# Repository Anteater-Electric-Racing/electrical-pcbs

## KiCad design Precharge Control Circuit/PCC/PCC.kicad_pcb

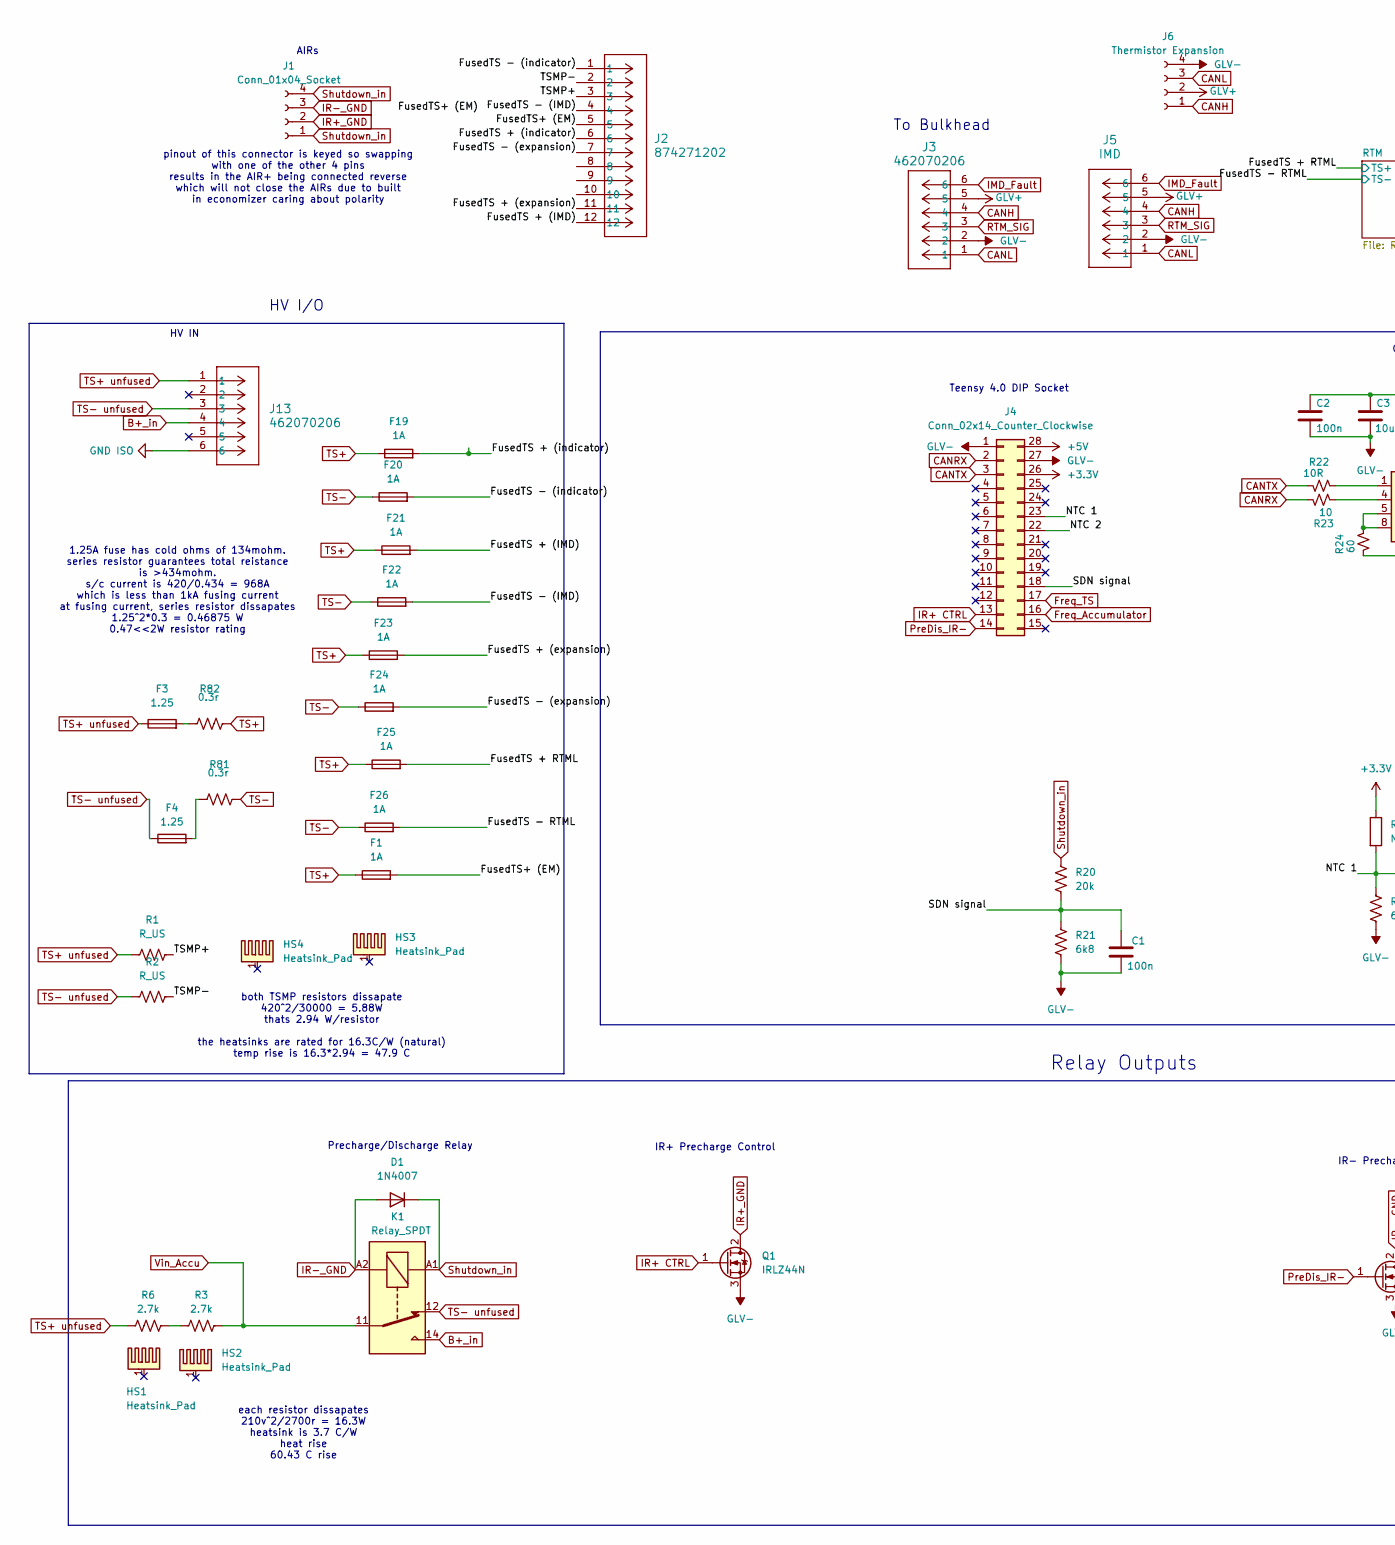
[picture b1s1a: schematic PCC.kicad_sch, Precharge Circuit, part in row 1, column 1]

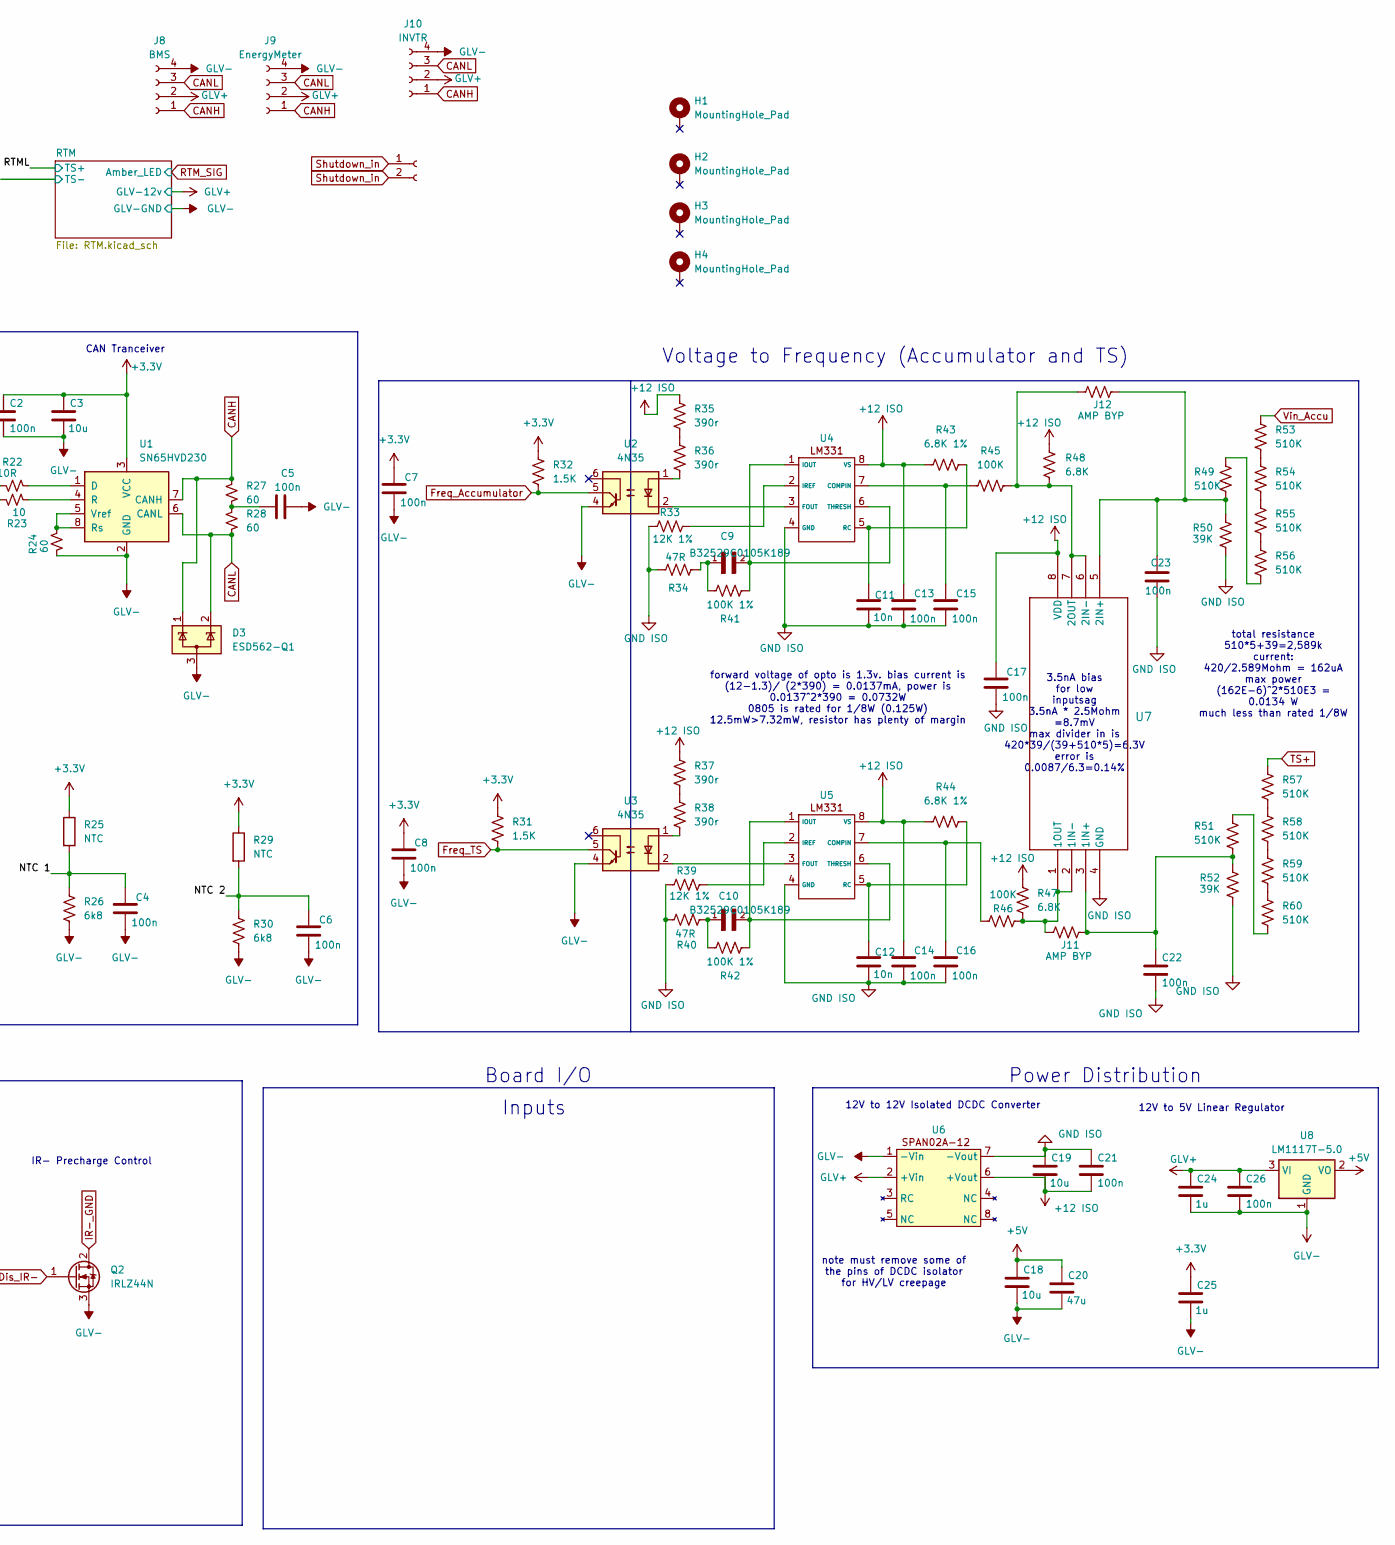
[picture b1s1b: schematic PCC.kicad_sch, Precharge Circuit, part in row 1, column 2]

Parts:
C1, C2, C4, C6, C7, C8, C13, C14, C15, C16, C17, C21, C22, C26: 100n; C_0805_2012Metric; MPN CC0805KRX7R9BB104
C3, C18, C19: 10u; C_0805_2012Metric; MPN EMK212BJ106KG-T
C5, C23: 100n; C_0805_2012Metric
C9, C10: B32529C0105K189; CAPRR500W50L730T450H950; PARTREV 2020-06; DigiKey_Part_Number 495-B32529C0105K189CT-ND
C11, C12: 10n; C_0805_2012Metric; MPN CL21B103KBANNNC
C20: 47u; C_0805_2012Metric; MPN GRM21BR61A476ME15K
C24, C25: 1u; C_0805_2012Metric; MPN CL21B105KBFNNNE
D1: 1N4007; D_DO-41_SOD81_P10.16mm_Horizontal; MPN 1N4007
D3: ESD562-Q1; SOT-23-3; MPN ESD562DBZRQ1
F1, F19, F20, F21, F22, F23, F24, F25, F26: 1A; 5x20fuseblock; MPN 0031.8222
F3, F4: 1.25; 5x20fuseblock; MPN 0031.8222
H1, H2, H3, H4: MountingHole_Pad; MountingHole_3.2mm_M3_DIN965_Pad_TopBottom
HS1, HS2: Heatsink_Pad; heatsink; MPN 529802B02500G
HS3, HS4: Heatsink_Pad; smolsink; MPN HSS-B20-0503H
J1: Conn_01x04_Socket; Molex_Mini-Fit_Jr_5566-04A2_2x02_P4.20mm_Vertical
J2: 874271202; 12pSTminifit
J3, J13: 462070206; 6pMinifitJR
J4: Conn_02x14_Counter_Clockwise; DIP-28_W15.24mm_Socket; MPN 110-44-628-41-001000
J5: IMD; 6pMinifitJR
J6: Thermistor Expansion; Molex_Mini-Fit_Jr_5566-04A2_2x02_P4.20mm_Vertical
J8: BMS; Molex_Mini-Fit_Jr_5566-04A2_2x02_P4.20mm_Vertical
J9: EnergyMeter; Molex_Mini-Fit_Jr_5566-04A2_2x02_P4.20mm_Vertical
J10: INVTR; Molex_Mini-Fit_Jr_5566-04A2_2x02_P4.20mm_Vertical
J11, J12: AMP BYP; R_0805_2012Metric
K1: Relay_SPDT; Precharge_Discharge_Relay_Rincon
Q1, Q2: IRLZ44N; TO-220-3_Horizontal_TabDown; MPN IRLZ44NPBF
R1, R2: R_US; TO-220-2_Vertical-SMD; MPN PWR220T-35-1502J
R3, R6: 2.7k; TO-220-2_Vertical; MPN RTO020F27000JTE3
R20: 20k; R_0805_2012Metric
R21, R26, R30: 6k8; R_0805_2012Metric
R22: 10R; R_0805_2012Metric
R23: 10; R_0805_2012Metric
R24, R27, R28: 60; R_0805_2012Metric
R25, R29: NTC; PinSocket_1x02_P2.00mm_Vertical
R31, R32: 1.5K; R_0805_2012Metric; MPN ERJ-6GEYJ152V
R33, R39: 12K 1%; R_0805_2012Metric; MPN CRG0805F12K
R34, R40: 47R; R_0805_2012Metric; MPN RC0805JR-0747RL
R35, R36, R37, R38: 390r; R_0805_2012Metric; MPN RC0805FR-7W390RL
R41, R42: 100K 1%; R_0805_2012Metric; MPN RMCF0805FG100K
R43, R44: 6.8K 1%; R_0805_2012Metric; MPN RC0805FR-076K8L
R45, R46: 100K; R_0805_2012Metric; MPN RMCF0805FG100K
R47, R48: 6.8K; R_0805_2012Metric; MPN RC0805FR-076K8L
R49, R51, R53, R54, R55, R56, R57, R58, R59, R60: 510K; R_0805_2012Metric; MPN ERJ-6GEYJ514V
R50, R52: 39K; R_0805_2012Metric; MPN ERJ-6GEYJ393V
R81, R82: 0.3r; R_2512_6332Metric_Pad1.40x3.35mm_HandSolder; MPN CSRN2512FKR300
SDC1: Conn_01x02_Socket; Molex_Mini-Fit_Jr_5566-02A2_2x01_P4.20mm_Vertical
U1: SN65HVD230; SOIC-8_3.9x4.9mm_P1.27mm; MPN SN65HVD230DR
U2, U3: 4N35; DIP-6_W7.62mm_Socket
U4, U5: DIP-8_W7.62mm_Socket; MPN Texas Instruments
U6: isoDCDC(removedPins); MPN SPAN02A-12
U7: TLV2372IP; P8; MPN TLV2372IP
U8: LM1117T-5.0; TO-220-3_Horizontal_TabDown; MPN LM1117T-5.0/NOPB

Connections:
+3.3V: C2.1, C3.1, C7.1, C8.1, C25.1, J4.26, R25.1, R29.1, R31.2, R32.2, U1.3 (VCC)
+5V: C18.1, C20.1, J4.28, U8.2 (VO)
+12 ISO: C13.1, C14.1, C17.1, C19.2, C21.2, R35.2, R37.2, R43.1, R44.1, R47.2, R48.2, U4.8 (VS), U5.8 (VS), U6.6 (+Vout), U7.8 (VDD)
/FusedTS + (IMD): F21.2, J2.12
/FusedTS + (expansion): F23.2, J2.11
/FusedTS + (indicator): F19.2, J2.6
/FusedTS - (IMD): F22.2, J2.4
/FusedTS - (expansion): F24.2, J2.7
/FusedTS - (indicator): F20.2, J2.1
/FusedTS+ (EM): F1.2, J2.5
/NTC 1: C4.1, J4.23, R25.2, R26.1
/NTC 2: C6.1, J4.22, R29.2, R30.1
/SDN signal: C1.1, J4.18, R20.2, R21.1
/TSMP+: J2.3, R1.1
/TSMP-: J2.2, R2.1
B+_in: J13.4, K1.14
CANH: D3.1 (K), J3.4, J5.4, J6.1, J8.1, J9.1, J10.1, R27.1, U1.7 (CANH)
CANL: D3.2 (K), J3.1, J5.1, J6.3, J8.3, J9.3, J10.3, R28.2, U1.6 (CANL)
CANRX: J4.2, R23.1
CANTX: J4.3, R22.2
Freq_Accumulator: J4.16, R32.1, U2.5
Freq_TS: J4.17, R31.1, U3.5
GLV+: C24.1, C26.1, J3.5, J5.5, J6.2, J8.2, J9.2, J10.2, U6.2 (+Vin), U8.3 (VI); also elsewhere on the board
GLV-: C1.2, C2.2, C3.2, C4.2, C5.2, C6.2, C7.2, C8.2, C18.2, C20.2, C24.2, C25.2, C26.2, D3.3 (A), J3.2, J4.1, J4.27, J5.2, J6.4, J8.4, J9.4, J10.4, Q1.3 (S), Q2.3 (S), R21.2, R24.2, R26.2, R30.2, U1.2 (GND), U2.4, U3.4, U6.1 (-Vin), U8.1 (GND); also elsewhere on the board
GND ISO: C11.2, C12.2, C13.2, C14.2, C15.2, C16.2, C17.2, C19.1, C21.1, C22.2, C23.2, J13.6, R33.1, R34.2, R39.1, R40.2, R50.2, R52.2, U4.4 (GND), U5.4 (GND), U6.7 (-Vout), U7.4 (GND)
HighVoltage+: F25.2; also elsewhere on the board
HighVoltage-: F26.2; also elsewhere on the board
IMD_Fault: J3.6, J5.6
IR+ CTRL: J4.13, Q1.1 (G)
IR+_GND: J1.2, Q1.2 (D)
IR-_GND: D1.2 (A), J1.3, K1.A2, Q2.2 (D)
unnamed: C5.1, R27.2, R28.1
unnamed: C9.1, R34.1, R41.1
unnamed: C10.1, R40.1, R42.1
unnamed: F3.2, R82.1
unnamed: F4.2, R81.1
unnamed: R3.1, R6.2
unnamed: R35.1, R36.2
unnamed: R36.1, U2.1
unnamed: R37.1, R38.2
unnamed: R38.1, U3.1
unnamed: R49.1, R56.2
unnamed: R51.1, R60.2
unnamed: R53.2, R54.1
unnamed: R54.2, R55.1
unnamed: R55.2, R56.1
unnamed: R57.2, R58.1
unnamed: R58.2, R59.1
unnamed: R59.2, R60.1
unnamed: R22.1, U1.1 (D)
unnamed: R23.2, U1.4 (R)
unnamed: R24.1, U1.5 (Vref), U1.8 (Rs)
unnamed: C15.1, R45.1, U4.7 (COMPIN)
unnamed: U2.2, U4.3 (FOUT)
unnamed: C9.2, R41.2, U4.1 (IOUT), U4.6 (THRESH)
unnamed: R33.2, U4.2 (IREF)
unnamed: C11.1, R43.2, U4.5 (RC)
unnamed: C16.1, R46.1, U5.7 (COMPIN)
unnamed: U3.2, U5.3 (FOUT)
unnamed: C10.2, R42.2, U5.1 (IOUT), U5.6 (THRESH)
unnamed: R39.2, U5.2 (IREF)
unnamed: C12.1, R44.2, U5.5 (RC)
unnamed: C22.1, J11.2, R51.2, R52.1, U7.3 (1IN+)
unnamed: J11.1, R46.2, R47.1, U7.1 (1OUT), U7.2 (1IN-)
unnamed: C23.1, J12.2, R49.2, R50.1, U7.5 (2IN+)
unnamed: J12.1, R45.2, R48.1, U7.6 (2IN-), U7.7 (2OUT)
PreDis_IR-: J4.14, Q2.1 (G)
RTM_SIG: J3.3, J5.3; also elsewhere on the board
Shutdown_in: D1.1 (K), J1.1, J1.4, K1.A1, R20.1, SDC1.1, SDC1.2
TS+: F1.1, F19.1, F21.1, F23.1, F25.1, R57.1, R82.2
TS+ unfused: F3.1, J13.1, R1.2, R6.1
TS-: F20.1, F22.1, F24.1, F26.1, R81.2
TS- unfused: F4.1, J13.3, K1.12, R2.2
Vin_Accu: K1.11, R3.2, R53.1

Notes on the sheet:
Board I/O
HV IN
HV I/O
total resistance 510*5+39=2,589k current: 420/2.589Mohm = 162uA max power (162E-6)^2*510E3 = 0.0134 W much less than rated 1/8W
Inputs
1.25A fuse has cold ohms of 134mohm. series resistor guarantees total reistance is >434mohm. s/c current is 420/0.434 = 968A which is less than 1kA fusing current at fusing current, series resistor dissapates 1.25^2*0.3 = 0.46875 W 0.47<<2W resistor rating
forward voltage of opto is 1.3v. bias current is (12-1.3)/ (2*390) = 0.0137mA, power is 0.0137^2*390 = 0.0732W 0805 is rated for 1/8W (0.125W) 12.5mW>7.32mW, resistor has plenty of margin
AIRs
each resistor dissapates 210v^2/2700r = 16.3W heatsink is 3.7 C/W heat rise 60.43 C rise
both TSMP resistors dissapate 420^2/30000 = 5.88W thats 2.94 W/resistor the heatsinks are rated for 16.3C/W (natural) temp rise is 16.3*2.94 = 47.9 C
To Bulkhead
Teensy 4.0 DIP Socket
IR- Precharge Control
Voltage to Frequency (Accumulator and TS)
3.5nA bias for low inputsag 3.5nA * 2.5Mohm =8.7mV max divider in is 420*39/(39+510*5)=6.3V error is 0.0087/6.3=0.14%
Relay Outputs
CAN Tranceiver
Precharge/Discharge Relay
note must remove some of the pins of DCDC isolator for HV/LV creepage
IR+ Precharge Control
Power Distribution
pinout of this connector is keyed so swapping with one of the other 4 pins results in the AIR+ being connected reverse which will not close the AIRs due to built in economizer caring about polarity
12V to 5V Linear Regulator
12V to 12V Isolated DCDC Converter

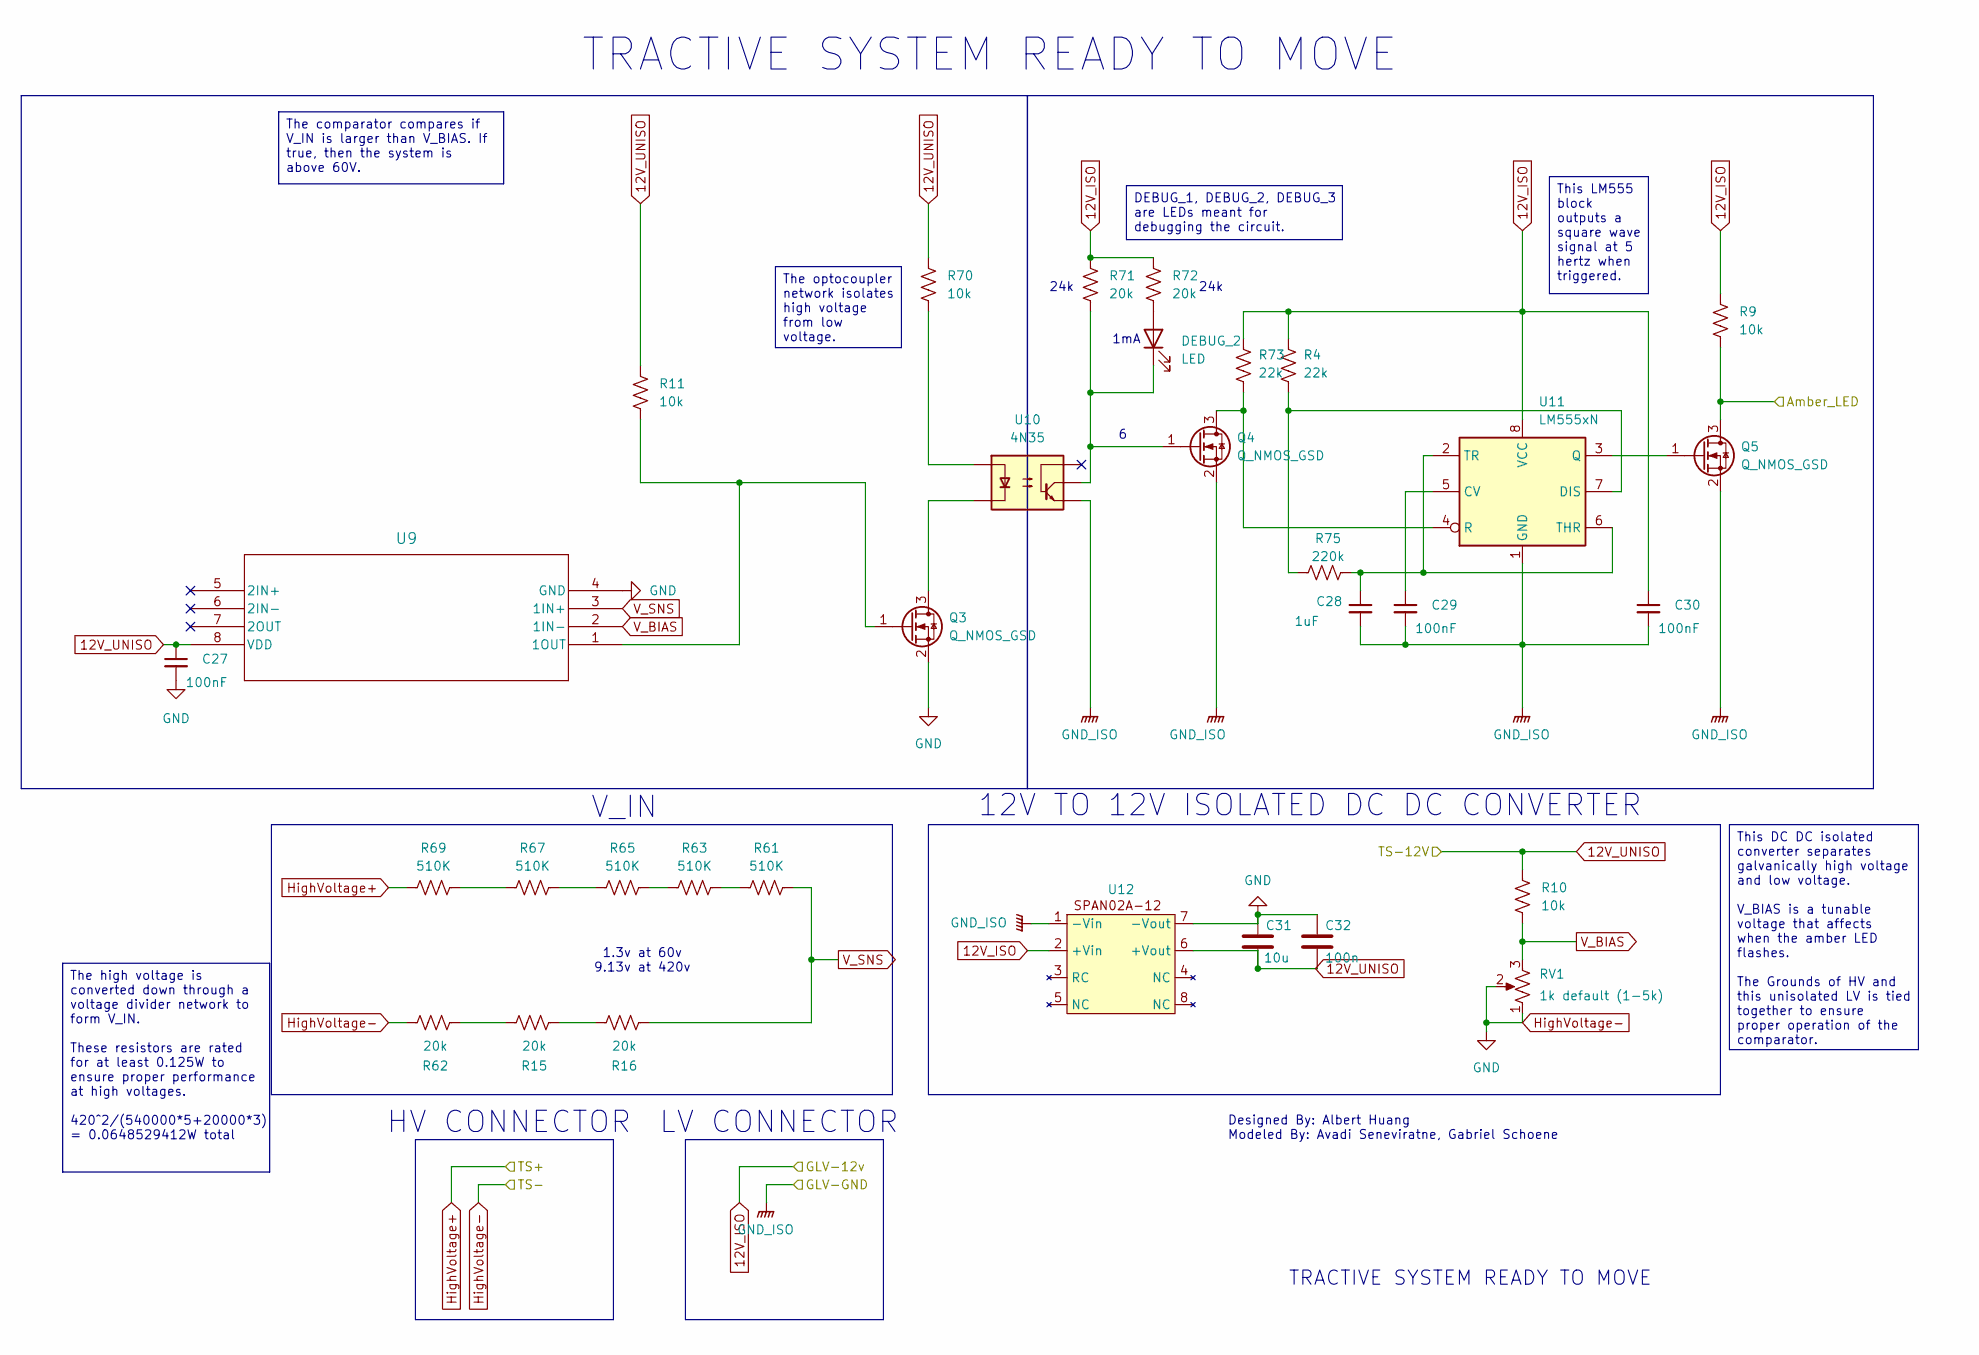
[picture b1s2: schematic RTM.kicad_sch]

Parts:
C27, C29, C30: 100nF; C_0805_2012Metric; MPN 08055C104J4T4A
C28: 1uF; C_0805_2012Metric; MPN CC0805JKX7R9BB105
C31: 10u; C_0805_2012Metric; MPN EMK212BJ106KG-T
C32: 100n; C_0805_2012Metric; MPN CC0805KRX7R9BB104
DEBUG_2: LED; LED_D5.0mm; MPN SLR-56VC3F
Q3, Q4, Q5: Q_NMOS_GSD; SOT-23; MPN SI2304A
R4, R73: 22k; R_0805_2012Metric; MPN RPC0805JT22R0
R9, R10, R11, R70: 10k; R_0805_2012Metric; MPN RC0805FR-7W10KL
R15, R16, R62: 20k; R_0805_2012Metric; MPN RC0805FR-0720KL
R61, R63, R65, R67, R69: 510K; R_0805_2012Metric; MPN ERJ-6GEYJ514V
R71, R72: 20k; R_0805_2012Metric
R75: 220k; R_0805_2012Metric; MPN RC0805FR-7W220KL
RV1: 1k default (1-5k); Potentiometer_Bourns_3296Y_Vertical; MPN 3296Y-1-502LF
U9: TLV2372IP; P8; MPN TLV2372IP
U10: 4N35; DIP-6_W7.62mm; MPN Lite-On Inc.
U11: LM555xN; DIP-8_W7.62mm
U12: isoDCDC(removedPins); MPN SPAN02A-12

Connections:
12V_UNISO: C27.1, C31.2, C32.2, R10.1, R11.1, R70.1, U9.8 (VDD), U12.6 (+Vout)
GLV+: C30.1, R4.1, R9.1, R71.1, R72.1, R73.1, U11.8 (VCC), U12.2 (+Vin); also elsewhere on the board
GLV-: C28.2, C29.2, C30.2, Q4.2 (S), Q5.2 (S), U10.4, U11.1 (GND), U12.1 (-Vin); also elsewhere on the board
HighVoltage+: R69.1; also elsewhere on the board
HighVoltage-: C27.2, C31.1, C32.1, Q3.2 (S), R62.2, RV1.1, RV1.2, U9.4 (GND), U12.7 (-Vout); also elsewhere on the board
unnamed: DEBUG_2.2 (A), R72.2
unnamed: DEBUG_2.1 (K), Q4.1 (G), R71.2, U10.5
unnamed: Q3.3 (D), U10.2
unnamed: Q3.1 (G), R11.2, U9.1 (1OUT)
unnamed: Q4.3 (D), R73.2, U11.4 (R)
unnamed: Q5.1 (G), U11.3 (Q)
unnamed: R15.1, R16.2
unnamed: R15.2, R62.1
unnamed: R61.1, R63.2
unnamed: R63.1, R65.2
unnamed: R65.1, R67.2
unnamed: R67.1, R69.2
unnamed: R70.2, U10.1
unnamed: C29.1, U11.5 (CV)
unnamed: R4.2, R75.1, U11.7 (DIS)
unnamed: C28.1, R75.2, U11.2 (TR), U11.6 (THR)
RTM_SIG: Q5.3 (D), R9.2; also elsewhere on the board
V_BIAS: R10.2, RV1.3, U9.2 (1IN-)
V_SNS: R16.1, R61.2, U9.3 (1IN+)

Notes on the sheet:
12V TO 12V ISOLATED DC DC CONVERTER
V_IN
1.3v at 60v 9.13v at 420v
TRACTIVE SYSTEM READY TO MOVE
24k
1mA
24k
LV CONNECTOR
TRACTIVE SYSTEM READY TO MOVE
Designed By: Albert Huang Modeled By: Avadi Seneviratne, Gabriel Schoene
HV CONNECTOR
This DC DC isolated converter separates galvanically high voltage and low voltage. V_BIAS is a tunable voltage that affects when the amber LED flashes. The Grounds of HV and this unisolated LV is tied together to ensure proper operation of the comparator.
The comparator compares if V_IN is larger than V_BIAS. If true, then the system is above 60V.
The high voltage is converted down through a voltage divider network to form V_IN. These resistors are rated for at least 0.125W to ensure proper performance at high voltages. 420^2/(540000*5+20000*3) = 0.0648529412W total
This LM555 block outputs a square wave signal at 5 hertz when triggered.
DEBUG_1, DEBUG_2, DEBUG_3 are LEDs meant for debugging the circuit.
The optocoupler network isolates high voltage from low voltage.

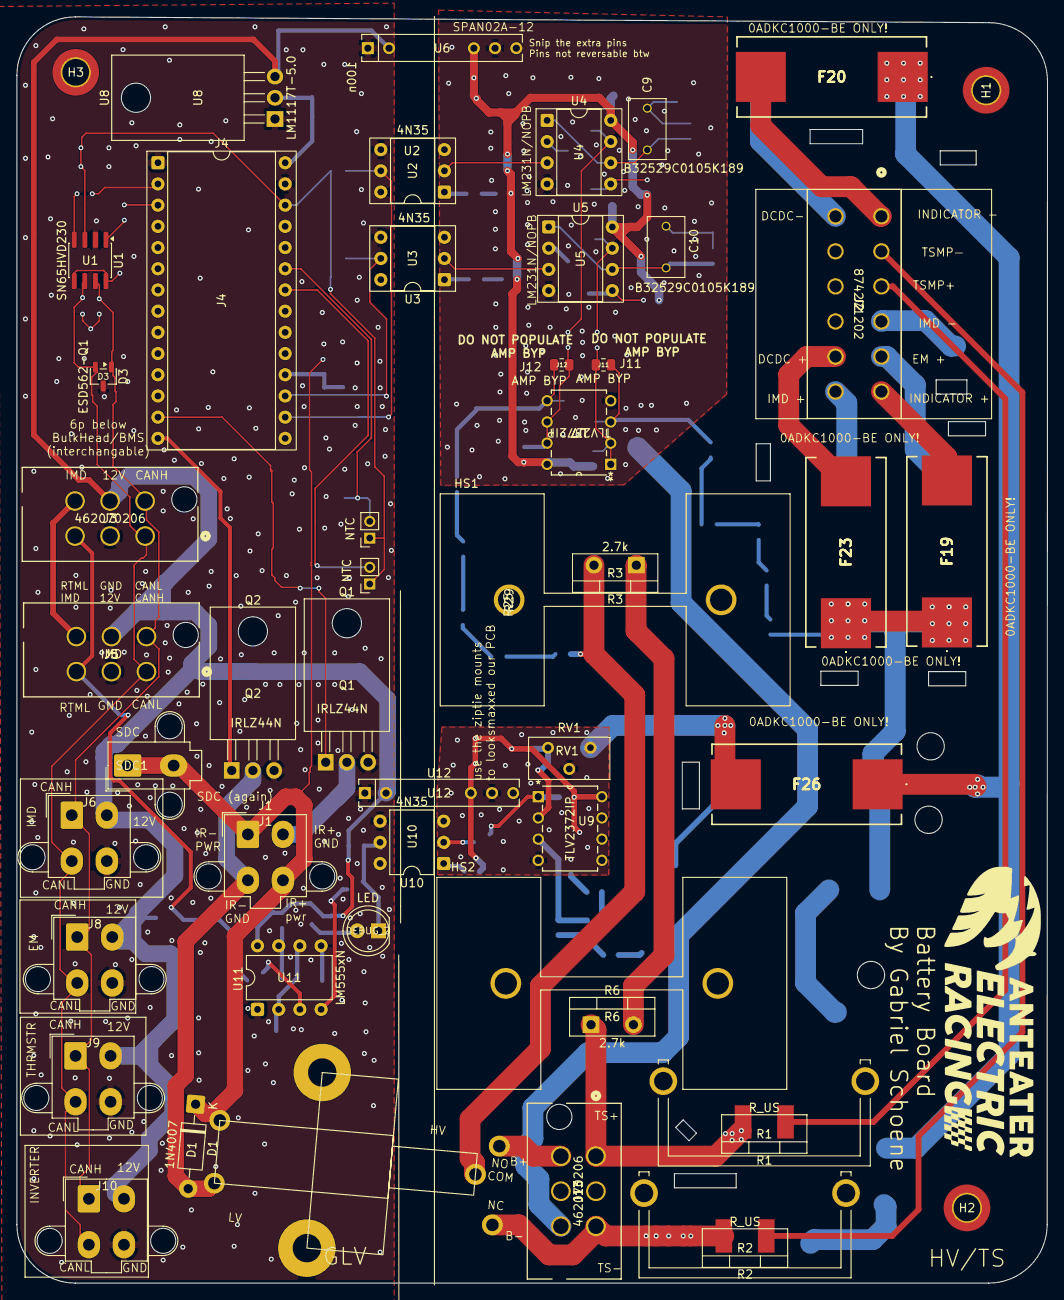
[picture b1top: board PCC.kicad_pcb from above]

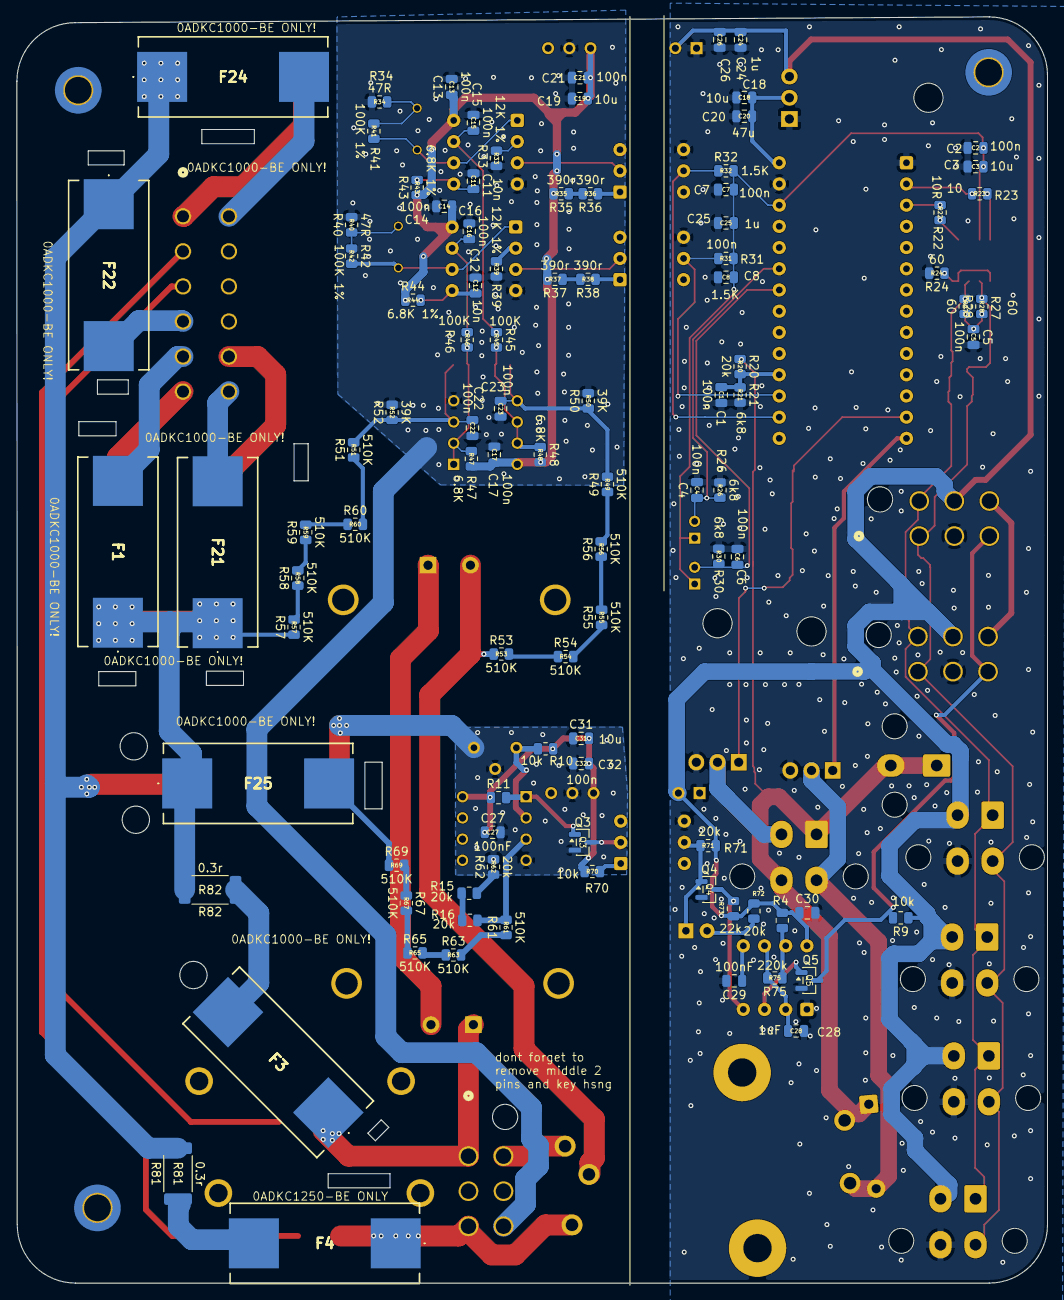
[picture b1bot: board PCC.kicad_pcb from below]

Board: 2 copper layers, 123.5 x 151.7 mm, 149 parts (98 on the bottom side), 93 nets.

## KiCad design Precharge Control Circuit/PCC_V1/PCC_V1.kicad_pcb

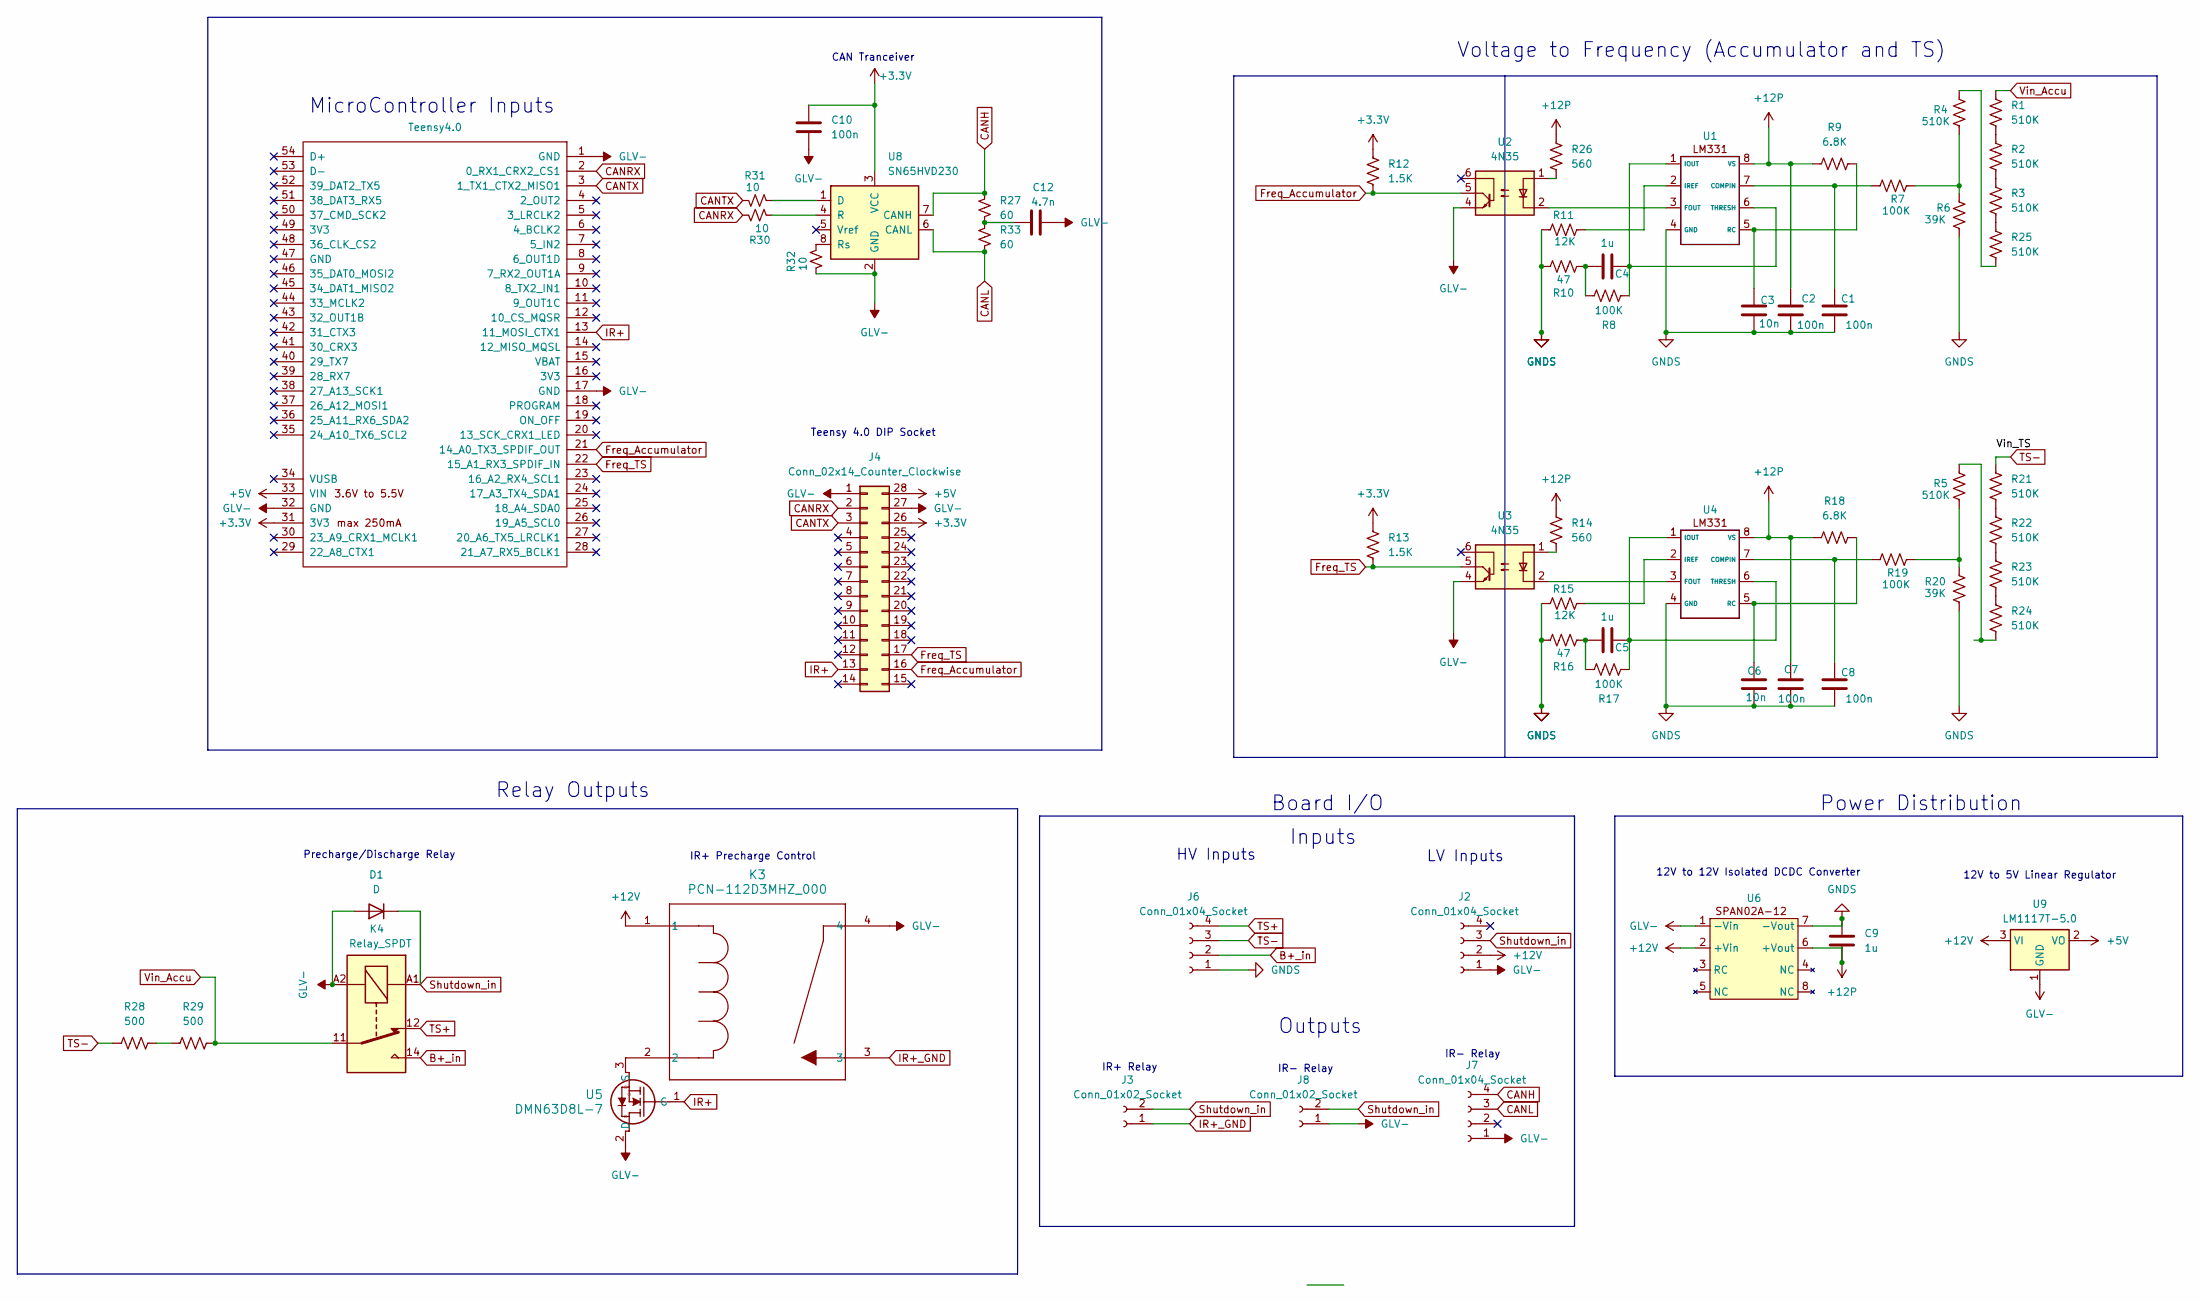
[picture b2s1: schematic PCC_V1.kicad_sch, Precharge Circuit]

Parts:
C1, C2, C7, C8, C10: 100n; C_0805_2012Metric
C3, C6: 10n; C_0805_2012Metric
C4, C5, C9: 1u; C_0805_2012Metric
C12: 4.7n; C_0805_2012Metric
D1: D; D_5KPW_P7.62mm_Vertical_AnodeUp
J2, J6, J7: Conn_01x04_Socket; Molex_Mini-Fit_Jr_5566-04A2_2x02_P4.20mm_Vertical
J3, J8: Conn_01x02_Socket; Molex_Mini-Fit_Jr_5566-02A2_2x01_P4.20mm_Vertical
J4: Conn_02x14_Counter_Clockwise; DIP-28_W15.24mm_Socket
K3: PCN-112D3MHZ_000; RELAY_PCN-105D3MHZ_000_TEC
K4: Relay_SPDT; Precharge_Discharge_Relay
R1, R2, R3, R4, R5, R21, R22, R23, R24, R25: 510K; R_0805_2012Metric
R6, R20: 39K; R_0805_2012Metric
R7, R8, R17, R19: 100K; R_0805_2012Metric
R9, R18: 6.8K; R_0805_2012Metric
R10, R16: 47; R_0805_2012Metric
R11, R15: 12K; R_0805_2012Metric
R12, R13: 1.5K; R_0805_2012Metric
R14, R26: 560; R_0805_2012Metric
R27, R33: 60; R_0805_2012Metric
R28, R29: 500; Ohmite HS100 500R F
R30, R31, R32: 10; R_0805_2012Metric
U1, U4: DIP-8_W7.62mm_Socket
U2, U3: 4N35; DIP-6_W7.62mm_Socket
U5: DMN63D8L-7; SOIC_63D8L-7_DIO
U6: SIP-8_19x3mm_P2.54mm
U7: Teensy4.0; DIP-28_W15.24mm_Socket
U8: SN65HVD230; SOIC-8_3.9x4.9mm_P1.27mm
U9: LM1117T-5.0; TO-220-3_Horizontal_TabDown

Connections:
+3.3V: C10.1, J4.26, R12.2, R13.2, U7.31 (3V3), U8.3 (VCC)
+5V: J4.28, U7.33 (VIN), U9.2 (VO)
+12P: C2.1, C7.1, C9.2, R9.1, R14.1, R18.1, R26.1, U1.8 (VS), U4.8 (VS), U6.6 (+Vout)
+12V: J2.2, K3.1, U6.2 (+Vin), U9.3 (VI)
B+_in: J6.2, K4.14
CANH: J7.4, R27.1, U8.7 (CANH)
CANL: J7.3, R33.2, U8.6 (CANL)
CANRX: J4.2, R30.1, U7.2 (0_RX1_CRX2_CS1)
CANTX: J4.3, R31.2, U7.3 (1_TX1_CTX2_MISO1)
Freq_Accumulator: J4.16, R12.1, U2.5, U7.21 (14_A0_TX3_SPDIF_OUT)
Freq_TS: J4.17, R13.1, U3.5, U7.22 (15_A1_RX3_SPDIF_IN)
GLV-: C10.2, C12.2, D1.2 (A), J2.1, J4.1, J4.27, J7.1, J8.1, K3.4, K4.A2, R32.2, U2.4, U3.4, U5.2 (D), U6.1 (-Vin), U7.1 (GND), U7.17 (GND), U7.32 (GND), U8.2 (GND), U9.1 (GND)
GNDS: C1.2, C2.2, C3.2, C6.2, C7.2, C8.2, C9.1, J6.1, R6.2, R10.2, R11.1, R15.1, R16.2, R20.2, U1.4 (GND), U4.4 (GND), U6.7 (-Vout)
IR+: J4.13, U5.1 (G), U7.13 (11_MOSI_CTX1)
IR+_GND: J3.1, K3.3
unnamed: C4.1, R8.1, R10.1
unnamed: C5.1, R16.1, R17.1
unnamed: C12.1, R27.2, R33.1
unnamed: R1.2, R2.1
unnamed: R2.2, R3.1
unnamed: R4.2, R6.1, R7.2
unnamed: R14.2, U3.1
unnamed: R5.2, R19.2, R20.1
unnamed: R21.2, R22.1
unnamed: R22.2, R23.1
unnamed: R23.2, R24.1
unnamed: R5.1, R24.2
unnamed: R3.2, R25.1
unnamed: R4.1, R25.2
unnamed: R26.2, U2.1
unnamed: R28.2, R29.1
unnamed: C1.1, R7.1, U1.7 (COMPIN)
unnamed: U1.3 (FOUT), U2.2
unnamed: C4.2, R8.2, U1.1 (IOUT), U1.6 (THRESH)
unnamed: R11.2, U1.2 (IREF)
unnamed: C3.1, R9.2, U1.5 (RC)
unnamed: C8.1, R19.1, U4.7 (COMPIN)
unnamed: U3.2, U4.3 (FOUT)
unnamed: C5.2, R17.2, U4.1 (IOUT), U4.6 (THRESH)
unnamed: R15.2, U4.2 (IREF)
unnamed: C6.1, R18.2, U4.5 (RC)
unnamed: K3.2, U5.3 (S)
unnamed: R31.1, U8.1 (D)
unnamed: R30.2, U8.4 (R)
unnamed: R32.1, U8.8 (Rs)
Shutdown_in: D1.1 (K), J2.3, J3.2, J8.2, K4.A1
TS+: J6.4, K4.12
TS-: J6.3, R21.1, R28.1
Vin_Accu: K4.11, R1.1, R29.2

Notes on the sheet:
Board I/O
HV Inputs
Inputs
IR+ Relay
LV Inputs
Teensy 4.0 DIP Socket
Voltage to Frequency (Accumulator and TS)
MicroController Inputs
IR- Relay
Relay Outputs
CAN Tranceiver
Precharge/Discharge Relay
IR+ Precharge Control
Outputs
Power Distribution
12V to 5V Linear Regulator
12V to 12V Isolated DCDC Converter

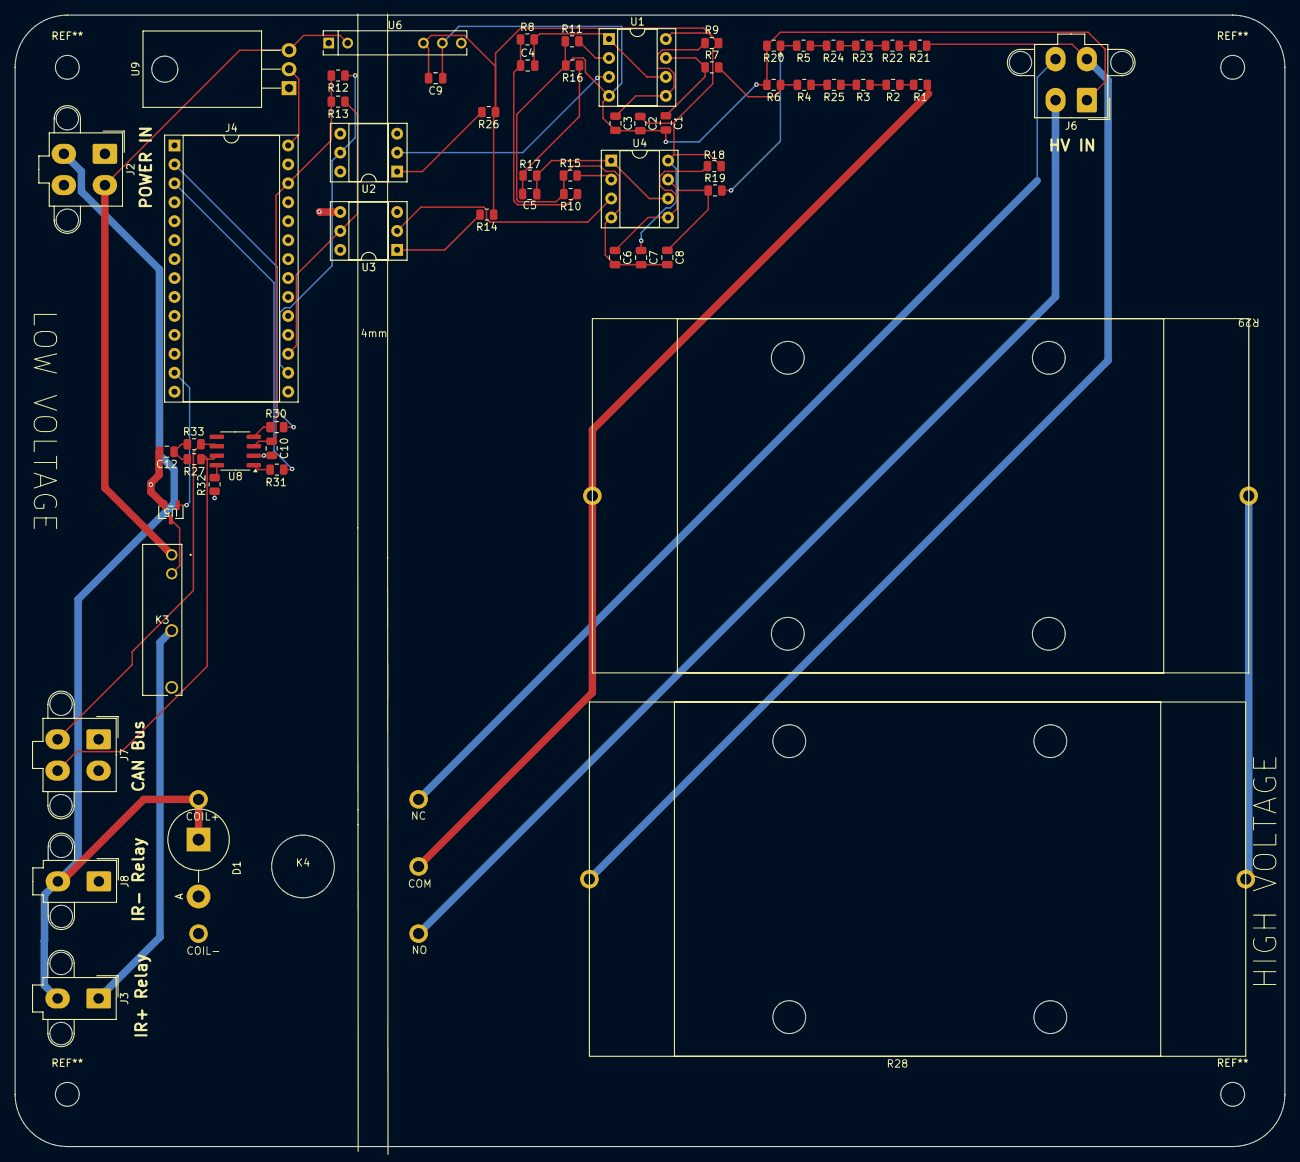
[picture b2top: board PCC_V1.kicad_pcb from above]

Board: 2 copper layers, 170.3 x 151.7 mm, 61 parts (0 on the bottom side), 49 nets.
